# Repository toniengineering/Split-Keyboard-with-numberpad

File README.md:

This is  a split keyboard with 43 keys a number pad. Each side of the split keyboard is running off of it's own xiao for the micro controller. The number pad will run off of a raspberry pi pico. The number pad has 20 keys, the first 17 will be the regular number pad keys and the extra 3 are for sound up, down and a pause button. The cad design for my PCB is a three part case that will connect using magnets that's why I have little rectangle in the side of them the magnets will be glued into them. The PCB will connect through screw holes in the case the half key board has three mounting holes while the number pad only has one but will still be screwed into the case. The case also has holes for the switches to pop out for keycaps and so I can press them. The case opens from the top and then should close with the PCB inside.

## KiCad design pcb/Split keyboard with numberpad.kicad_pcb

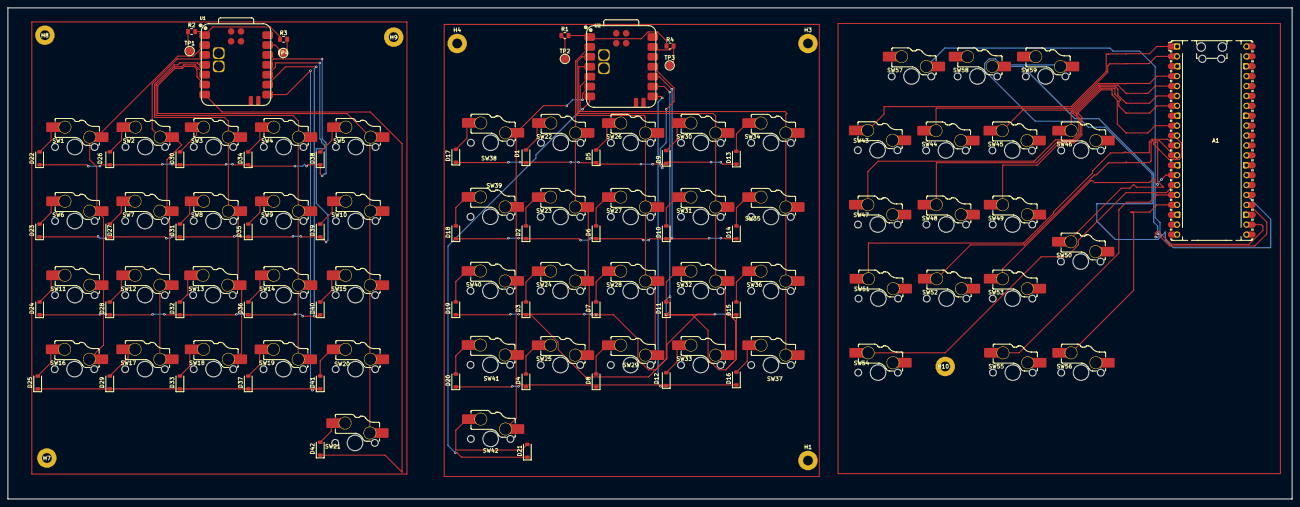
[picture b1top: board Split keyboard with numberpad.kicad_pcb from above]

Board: 2 copper layers, 329.5 x 126.0 mm, 119 parts (0 on the bottom side), 84 nets.

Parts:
A1: RaspberryPi_Pico; RaspberryPi_Pico_Common_Unspecified
D1, D2, D3, D4, D5, D6, D7, D8, D9, D10, D11, D12, D13, D14, D15, D16, D17, D18, D19, D20, D21, D22, D23, D24, D25, D26, D27, D28, D29, D30, D31, D32, D33, D34, D35, D36, D37, D38, D39, D40, D41, D42: D; D_SOD-123
H1, H3, H4, H7, H8, H9, H10: MountingHole; MountingHole_2.5mm_Pad
R1, R2: 806k; R_0805_2012Metric
R3, R4: 2M; R_0805_2012Metric
SW1, SW2, SW3, SW4, SW5, SW6, SW7, SW8, SW9, SW10, SW11, SW12, SW13, SW14, SW15, SW16, SW17, SW18, SW19, SW20, SW21, SW22, SW23, SW24, SW25, SW26, SW27, SW28, SW29, SW30, SW31, SW32, SW33, SW34, SW35, SW36, SW37, SW38, SW39, SW40, SW41, SW42, SW43, SW44, SW45, SW46, SW47, SW48, SW49, SW50, SW51, SW52, SW53, SW54, SW55, SW56, SW57, SW58, SW59: SW_Push; SW_MX_HS_KS-2P02B01-01_1.75u
TP1, TP2: BAT; TestPoint_Pad_D2.0mm
TP3, TP4: GND; TestPoint_Pad_D2.0mm
U1, U2: XIAO-nRF52840-SMD; modified-XIAO-nRF52840-SMD

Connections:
/left/BT_Pin: R2.2, R3.1, U1.1 (P0.02_A0_D0)
/left/VBAT: R2.1, TP1.1 (1_1)
/left/col0: SW1.1, SW6.1, SW11.1, SW16.1, U1.2 (P0.03_A1_D1)
/left/col1: SW2.1, SW7.1, SW12.1, SW17.1, U1.3 (P0.28_A2_D2)
/left/col2: SW3.1, SW8.1, SW13.1, SW18.1, U1.4 (P0.29_A3_D3)
/left/col3: SW4.1, SW9.1, SW14.1, SW19.1, U1.5 (P0.04_A4_D4_SDA)
/left/col4: SW5.1, SW10.1, SW15.1, SW20.1, SW21.1, U1.6 (P0.05_A5_D5_SCL)
/left/row0: D22.1 (K), D26.1 (K), D30.1 (K), D34.1 (K), D38.1 (K), U1.11 (P1.15_D10_MOSI)
/left/row1: D23.1 (K), D27.1 (K), D31.1 (K), D35.1 (K), D39.1 (K), U1.10 (P1.14_D9_MISO)
/left/row2: D24.1 (K), D28.1 (K), D32.1 (K), D36.1 (K), D40.1 (K), U1.9 (P1.13_D8_SCK)
/left/row3: D25.1 (K), D29.1 (K), D33.1 (K), D37.1 (K), D41.1 (K), U1.8 (P1.12_D7_RX)
/left/row4: D42.1 (K), U1.7 (P1.11_D6_TX)
/right/BT_Pin: R1.2, R4.1, U2.1 (P0.02_A0_D0)
/right/VBAT: R1.1, TP2.1 (1_1)
/right/col0: SW22.1, SW23.1, SW24.1, SW25.1, U2.2 (P0.03_A1_D1)
/right/col1: SW26.1, SW27.1, SW28.1, SW29.1, U2.3 (P0.28_A2_D2)
/right/col2: SW30.1, SW31.1, SW32.1, SW33.1, U2.4 (P0.29_A3_D3)
/right/col3: SW34.1, SW35.1, SW36.1, SW37.1, U2.5 (P0.04_A4_D4_SDA)
/right/col4: SW38.1, SW39.1, SW40.1, SW41.1, SW42.1, U2.6 (P0.05_A5_D5_SCL)
/right/row0: D1.1 (K), D5.1 (K), D9.1 (K), D13.1 (K), D17.1 (K), U2.11 (P1.15_D10_MOSI)
/right/row1: D2.1 (K), D6.1 (K), D10.1 (K), D14.1 (K), D18.1 (K), U2.10 (P1.14_D9_MISO)
/right/row2: D3.1 (K), D7.1 (K), D11.1 (K), D15.1 (K), D19.1 (K), U2.9 (P1.13_D8_SCK)
/right/row3: D4.1 (K), D8.1 (K), D12.1 (K), D16.1 (K), D20.1 (K), U2.8 (P1.12_D7_RX)
/right/row4: D21.1 (K), U2.7 (P1.11_D6_TX)
GND: A1.3 (GND), A1.8 (GND), A1.13 (GND), A1.18 (GND), A1.23 (GND), A1.28 (GND), A1.38 (GND), R3.2, R4.2, TP3.1 (1_1), TP4.1 (1_1), U1.13 (GND), U2.13 (GND)
unnamed: A1.1 (GPIO0), SW43.2 (2_2)
unnamed: A1.2 (GPIO1), SW44.2 (2_2)
unnamed: A1.4 (GPIO2), SW45.2 (2_2)
unnamed: A1.5 (GPIO3), SW46.2 (2_2)
unnamed: A1.6 (GPIO4), SW47.2 (2_2)
unnamed: A1.7 (GPIO5), SW48.2 (2_2)
unnamed: A1.9 (GPIO6), SW49.2 (2_2)
unnamed: A1.10 (GPIO7), SW50.2 (2_2)
unnamed: A1.11 (GPIO8), SW51.2 (2_2)
unnamed: A1.12 (GPIO9), SW52.2 (2_2)
unnamed: A1.14 (GPIO10), SW53.2 (2_2)
unnamed: A1.15 (GPIO11), SW54.2 (2_2)
unnamed: A1.16 (GPIO12), SW55.2 (2_2)
unnamed: A1.17 (GPIO13), SW56.2 (2_2)
unnamed: A1.22 (GPIO17), SW57.1 (1_1)
unnamed: A1.24 (GPIO18), SW58.1 (1_1)
unnamed: A1.25 (GPIO19), SW59.1 (1_1)
unnamed: D1.2 (A), SW22.2
unnamed: D2.2 (A), SW23.2
unnamed: D3.2 (A), SW24.2
unnamed: D4.2 (A), SW25.2
unnamed: D5.2 (A), SW26.2
unnamed: D6.2 (A), SW27.2
unnamed: D7.2 (A), SW28.2
unnamed: D8.2 (A), SW29.2
unnamed: D9.2 (A), SW30.2
unnamed: D10.2 (A), SW31.2
unnamed: D11.2 (A), SW32.2
unnamed: D12.2 (A), SW33.2
unnamed: D13.2 (A), SW34.2
unnamed: D14.2 (A), SW35.2
unnamed: D15.2 (A), SW36.2
unnamed: D16.2 (A), SW37.2
unnamed: D17.2 (A), SW38.2
unnamed: D18.2 (A), SW39.2
unnamed: D19.2 (A), SW40.2
unnamed: D20.2 (A), SW41.2
unnamed: D21.2 (A), SW42.2
unnamed: D22.2 (A), SW1.2
unnamed: D23.2 (A), SW6.2
unnamed: D24.2 (A), SW11.2
unnamed: D25.2 (A), SW16.2
unnamed: D26.2 (A), SW2.2
unnamed: D27.2 (A), SW7.2
unnamed: D28.2 (A), SW12.2
unnamed: D29.2 (A), SW17.2
unnamed: D30.2 (A), SW3.2
unnamed: D31.2 (A), SW8.2
unnamed: D32.2 (A), SW13.2
unnamed: D33.2 (A), SW18.2
unnamed: D34.2 (A), SW4.2
unnamed: D35.2 (A), SW9.2
unnamed: D36.2 (A), SW14.2
unnamed: D37.2 (A), SW19.2
unnamed: D38.2 (A), SW5.2
unnamed: D39.2 (A), SW10.2
unnamed: D40.2 (A), SW15.2
unnamed: D41.2 (A), SW20.2
unnamed: D42.2 (A), SW21.2
